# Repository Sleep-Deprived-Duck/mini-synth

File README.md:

# mini-synth
a small capacitive touch synthesizer keypad

Modeled with KiCad and Fusion360

Main functions are all on the PCB, screwed into a simple case

Features:

Basic volume and pitch controls using rotary encoders as knobs

Note glide duration and glide speed controls using 2 potentiometers

4 LEDs that can be programmed with various colours as indicators and such

Keyboard inputs with 7 touch keys

All reprogrammable to preference

Planned for use with a simple DAWS as an input device

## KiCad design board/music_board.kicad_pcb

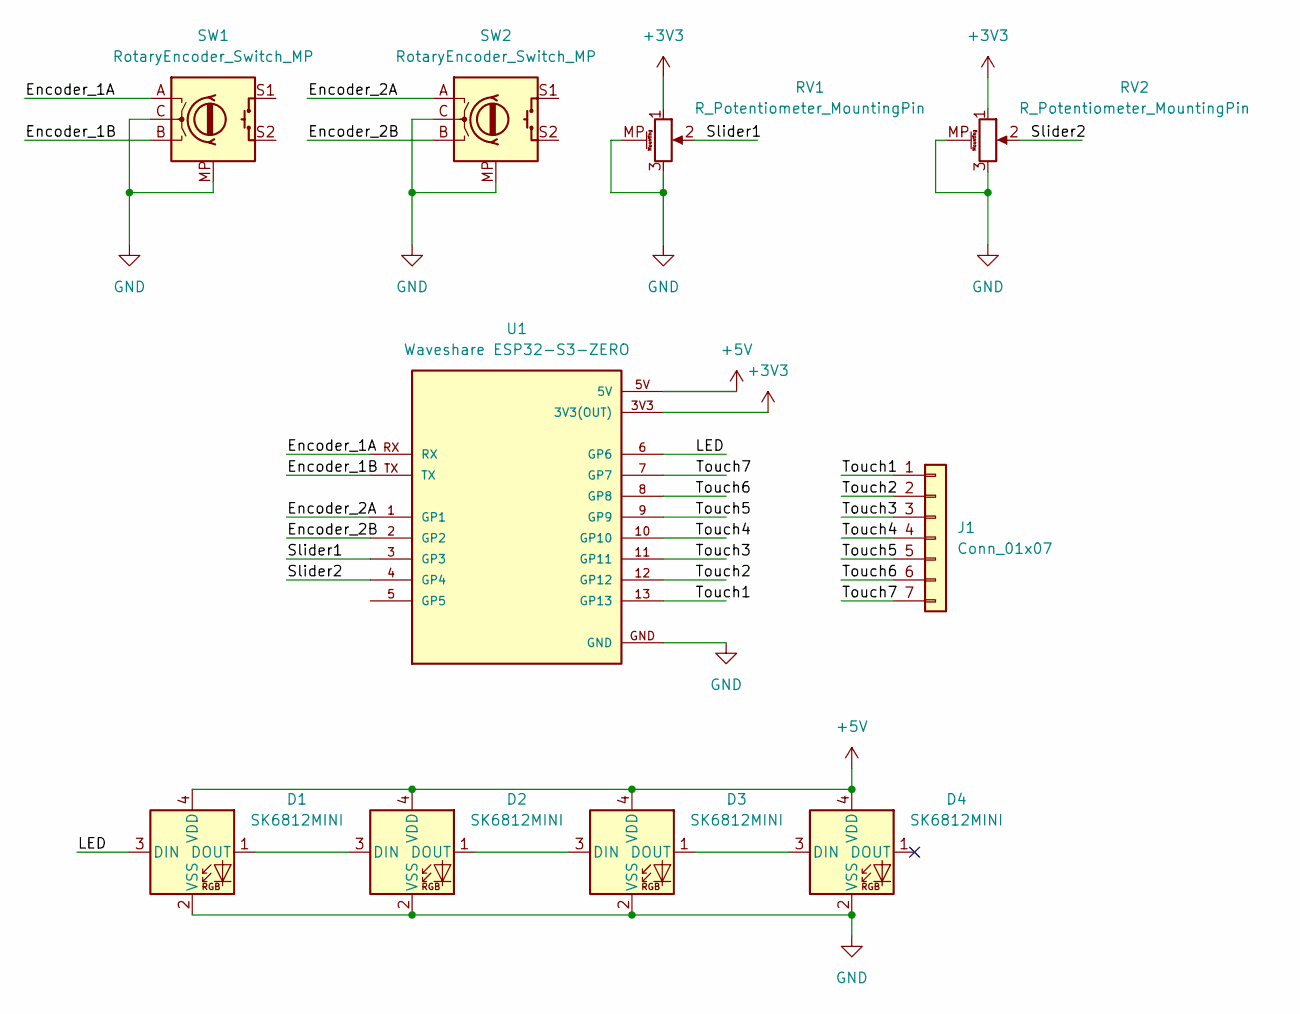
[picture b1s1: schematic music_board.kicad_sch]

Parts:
D1, D2, D3, D4: SK6812MINI; LED_SK6812MINI_PLCC4_3.5x3.5mm_P1.75mm
J1: Conn_01x07; Untitled
RV1, RV2: R_Potentiometer_MountingPin; Potentiometer_Bourns_PTA1543_Single_Slide
SW1, SW2: RotaryEncoder_Switch_MP; RotaryEncoder_Alps_EC11E-Switch_Vertical_H20mm_MountingHoles
U1: Waveshare ESP32-S3-ZERO; Waveshare ESP32-S3-Zero; PARTREV NA

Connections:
+3V3: RV1.1, RV2.1, U1.3V3 (3V3(OUT))
+5V: D1.4 (VDD), D2.4 (VDD), D3.4 (VDD), D4.4 (VDD), U1.5V
/Encoder_1A: SW1.A, U1.RX
/Encoder_1B: SW1.B, U1.TX
/Encoder_2A: SW2.A, U1.1 (GP1)
/Encoder_2B: SW2.B, U1.2 (GP2)
/LED: D1.3 (DIN), U1.6 (GP6)
/Slider1: RV1.2, U1.3 (GP3)
/Slider2: RV2.2, U1.4 (GP4)
/Touch1: J1.1, U1.13 (GP13)
/Touch2: J1.2, U1.12 (GP12)
/Touch3: J1.3, U1.11 (GP11)
/Touch4: J1.4, U1.10 (GP10)
/Touch5: J1.5, U1.9 (GP9)
/Touch6: J1.6, U1.8 (GP8)
/Touch7: J1.7, U1.7 (GP7)
GND: D1.2 (VSS), D2.2 (VSS), D3.2 (VSS), D4.2 (VSS), RV1.3, RV1.MP (MountPin), RV2.3, RV2.MP (MountPin), SW1.C, SW1.MP, SW2.C, SW2.MP, U1.GND
unnamed: D1.1 (DOUT), D2.3 (DIN)
unnamed: D2.1 (DOUT), D3.3 (DIN)
unnamed: D3.1 (DOUT), D4.3 (DIN)

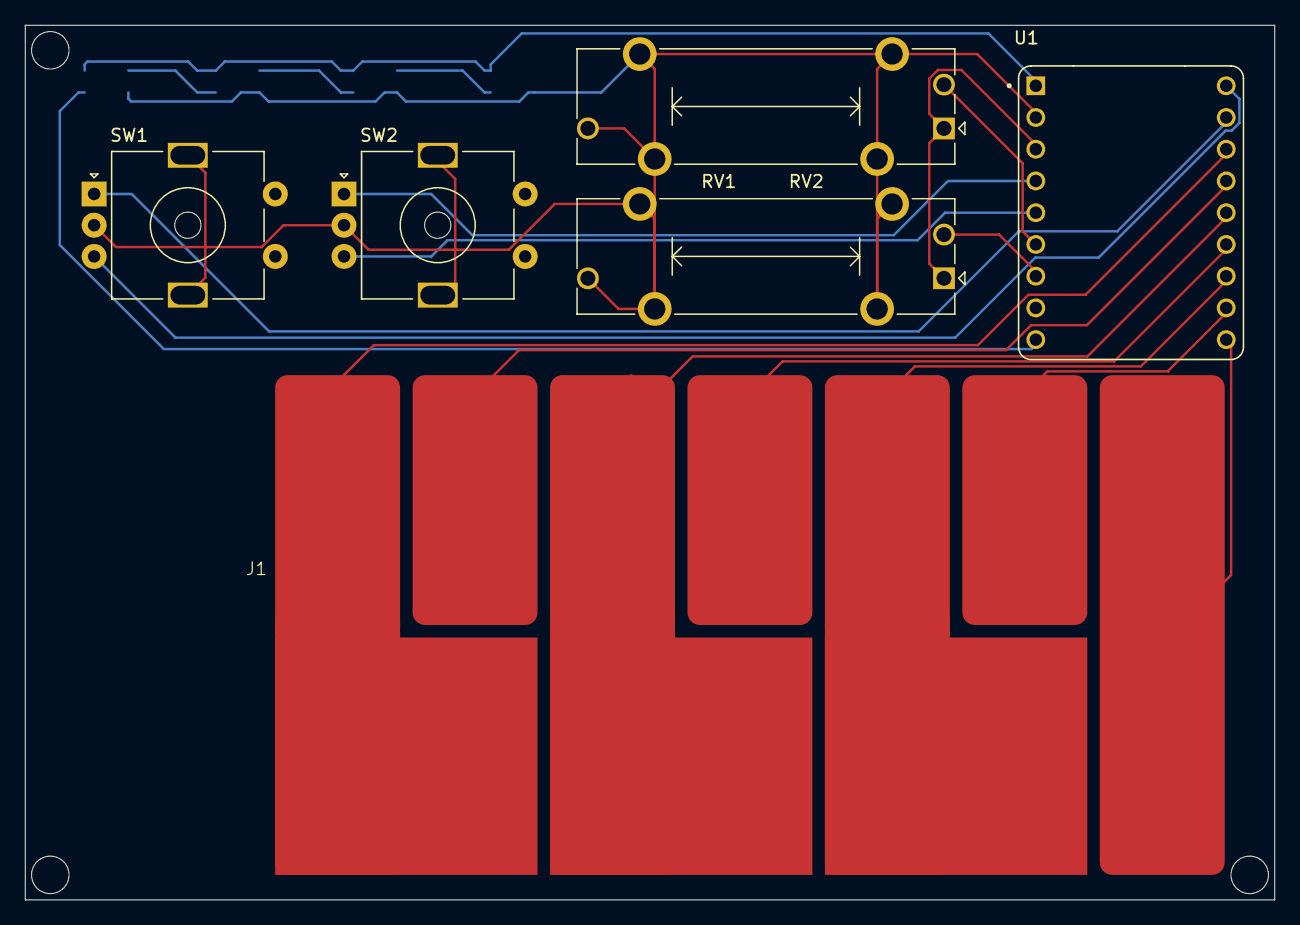
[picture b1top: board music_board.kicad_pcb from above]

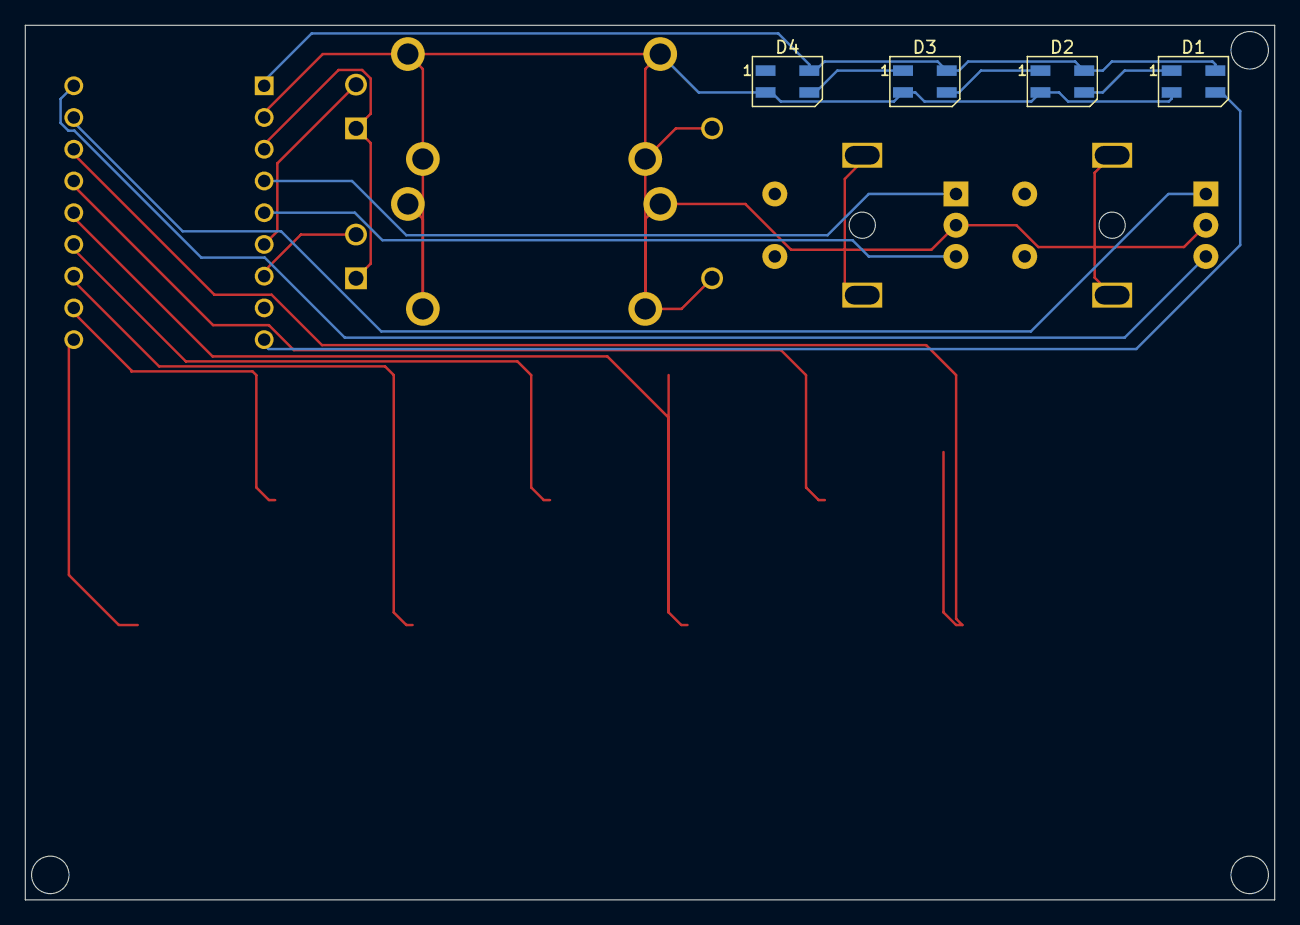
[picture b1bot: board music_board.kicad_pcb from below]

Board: 2 copper layers, 100.0 x 70.0 mm, 10 parts (4 on the bottom side), 20 nets.
